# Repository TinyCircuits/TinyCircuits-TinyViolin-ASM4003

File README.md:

# TinyCircuits TinyViolin
# ASM4003 Rev1

The design files are located under design_files/ for the TinyCircuits ASM4003 Rev 1 PCB.  This is a Tiny Violin with capacitive touch sensors and a buzzer.

Format is in Cadsoft Eagle format - Eagle version 6.2 was used for the original design.

For more infomation on this, check out the product page at TinyCircuits.com:  https://tinycircuits.com/collections/kits/products/tiny-violin

# License:

Design by TinyCircuits.
All design files are released under the Creative Commons Attribution Share-Alike 3.0 License, see the following link for details: http://creativecommons.org/licenses/by-sa/3.0

All text above must be included in any redistribution or derived design

This project uses designs and concepts developed as part of the Arduino project and the LilyPad project.  The TinyCircuits design files themselves (schematics, PCB and libraries) are not directly derived from these works' design files and have been created new, however the concepts and basic architecture behind the TinyDuino and TinyLily products are derived and we thank the hard work of the organizations below for their contributions to open-source hardware:
  
Original Arduino Uno Design by Team Arduino

LilyPad Arduino Design by Leah Buechley and Sparkfun Electronics

Please support the open-source hardware community

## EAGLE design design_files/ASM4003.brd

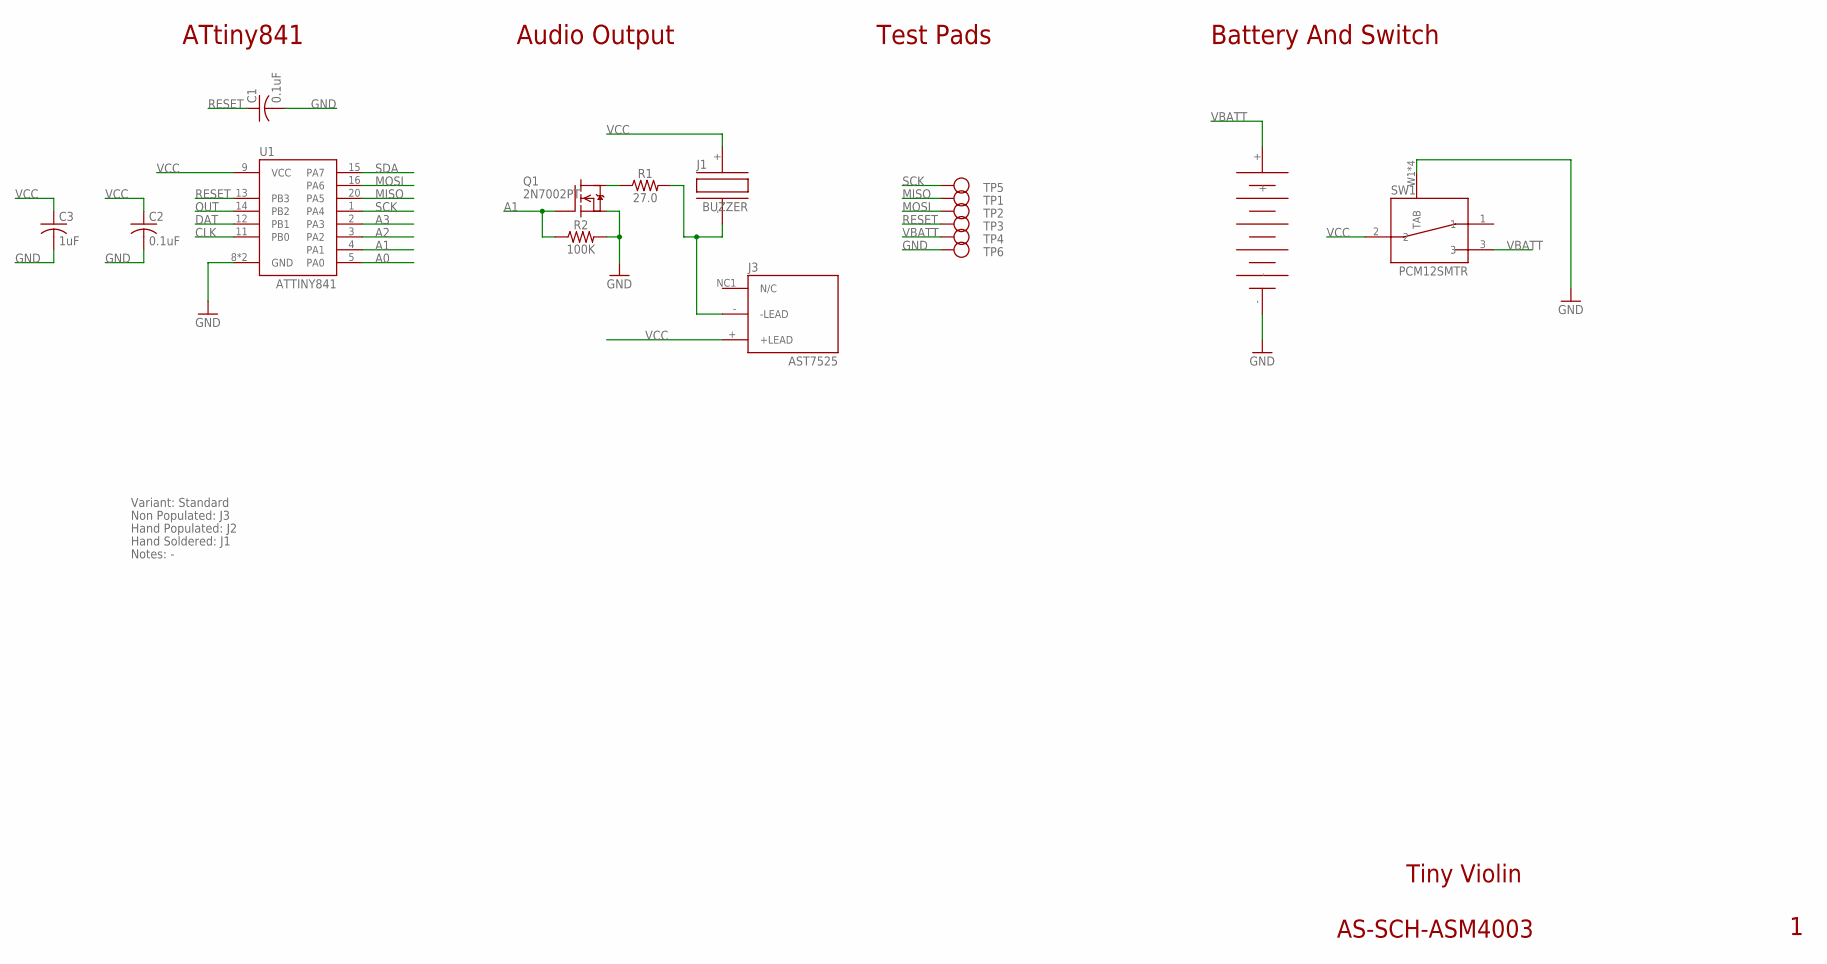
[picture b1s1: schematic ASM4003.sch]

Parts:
C1: 0.1uF; C0402; PARTNO AS-ITM-00008
C2: 0.1uF; C0402
C3: 1uF; C0402
J1: BUZZER; BUZZER_12MM
J2: 1225; COIN_1220_SMD; PARTNO AS-ITM-00468
J3: AST7525
Q1: 2N7002PT; SOT-416
R1: 27.0; 0402
R2: 100K; 0402
SW1: PCM12SMTR; PARTNO AS-ITM-00469
TP1, TP2, TP3, TP4, TP5, TP6: TEST_POINT; TEST_POINT_1MM
U1: ATTINY841; VQFN-20

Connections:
A0: U1.5 (PA0)
A1: Q1.1 (G), R2.1, U1.4 (PA1)
A2: U1.3 (PA2)
A3: U1.2 (PA3)
CLK: U1.11 (PB0)
DAT: U1.12 (PB1)
GND: C1.2, C2.2, C3.2, J2.-, Q1.2 (S), R2.2, SW1.W1 (TAB), SW1.W2 (TAB), SW1.W3 (TAB), SW1.W4 (TAB), TP6.P$1, U1.8 (GND), U1.PAD (GND)
MISO: TP1.P$1, U1.20 (PA5)
MOSI: TP2.P$1, U1.16 (PA6)
unnamed: Q1.3 (D), R1.1
unnamed: J1.- (2), J3.- (-LEAD), R1.2
OUT: U1.14 (PB2)
RESET: C1.1, TP3.P$1, U1.13 (PB3)
SCK: TP5.P$1, U1.1 (PA4)
SDA: U1.15 (PA7)
VBATT: J2.+, SW1.3, TP4.P$1
VCC: C2.1, C3.1, J1.+ (1), J3.+ (+LEAD), SW1.2, U1.9 (VCC)

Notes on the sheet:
Tiny Violin
AS-SCH-ASM4003
Test Pads
ATtiny841
Battery And Switch
Audio Output
Variant: Standard
Non Populated: J3
Hand Populated: J2
Hand Soldered: J1
Notes: -

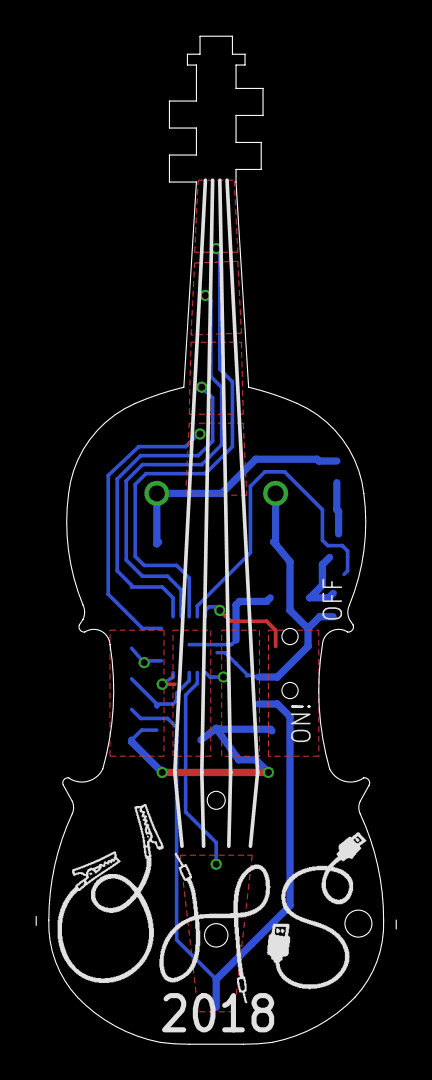
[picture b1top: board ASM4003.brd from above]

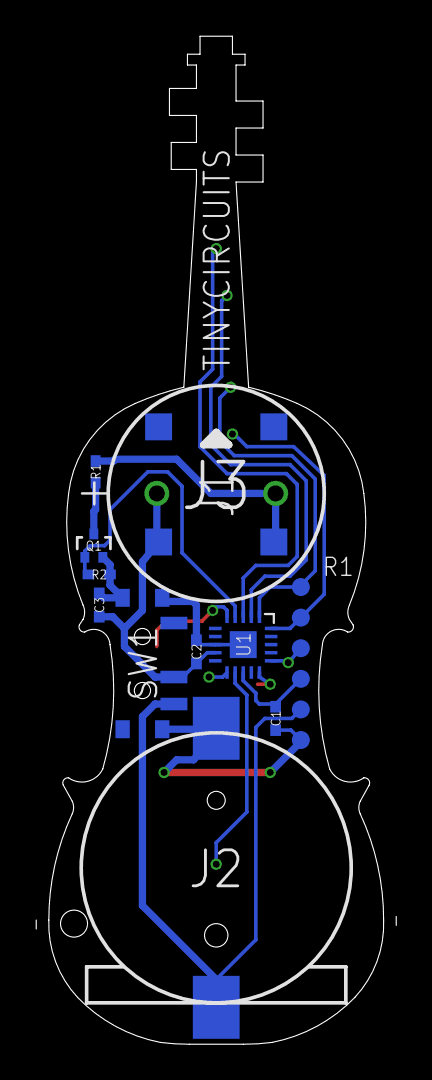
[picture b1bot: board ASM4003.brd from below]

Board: 2 copper layers, 20.0 x 56.0 mm, 18 parts (17 on the bottom side), 10 nets.

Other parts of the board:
U$1: DOCFIELD-TINYCIRCUITS-PCB

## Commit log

2019-01-02 update format
2019-08-02 pics
